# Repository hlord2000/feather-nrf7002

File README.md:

nRF7002/nRF5340 in Feather Formfactor
 * SD Card
 * Onboard flash
 * STEMMA Qt/Qwiic I2C connector
 * USB-C
 * nPM1300 regulator/battery charger

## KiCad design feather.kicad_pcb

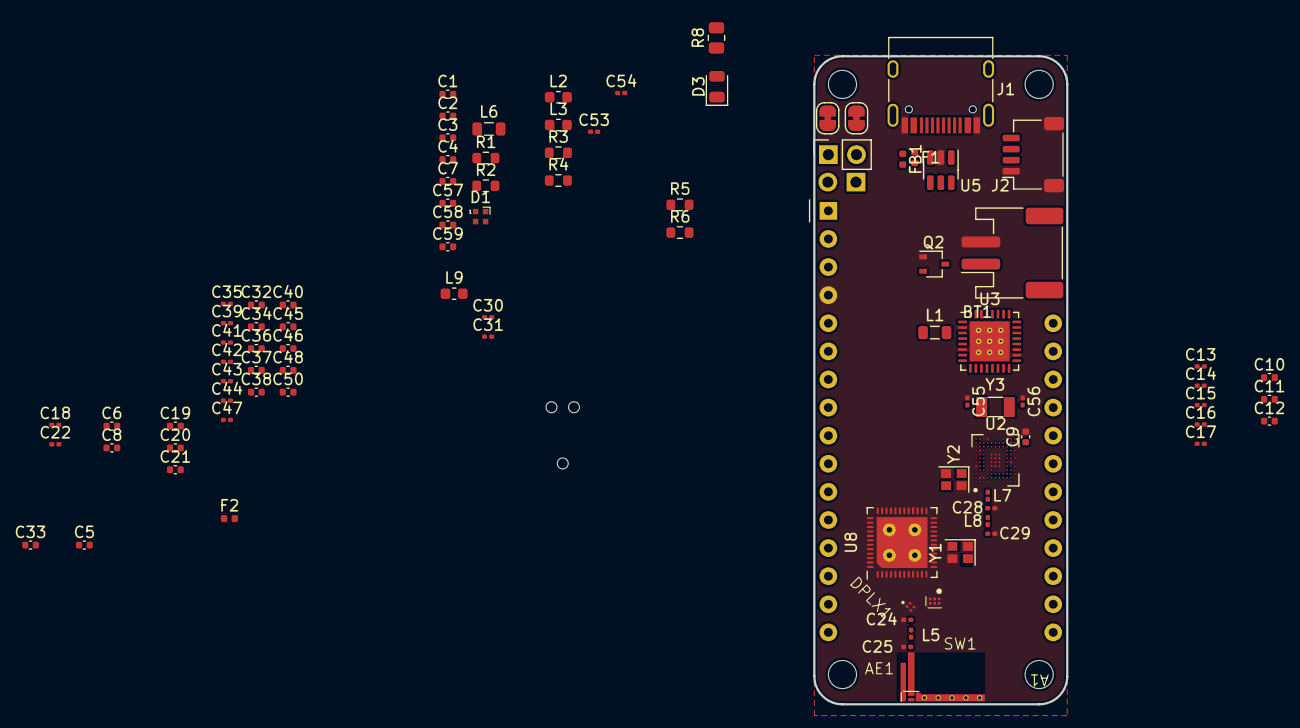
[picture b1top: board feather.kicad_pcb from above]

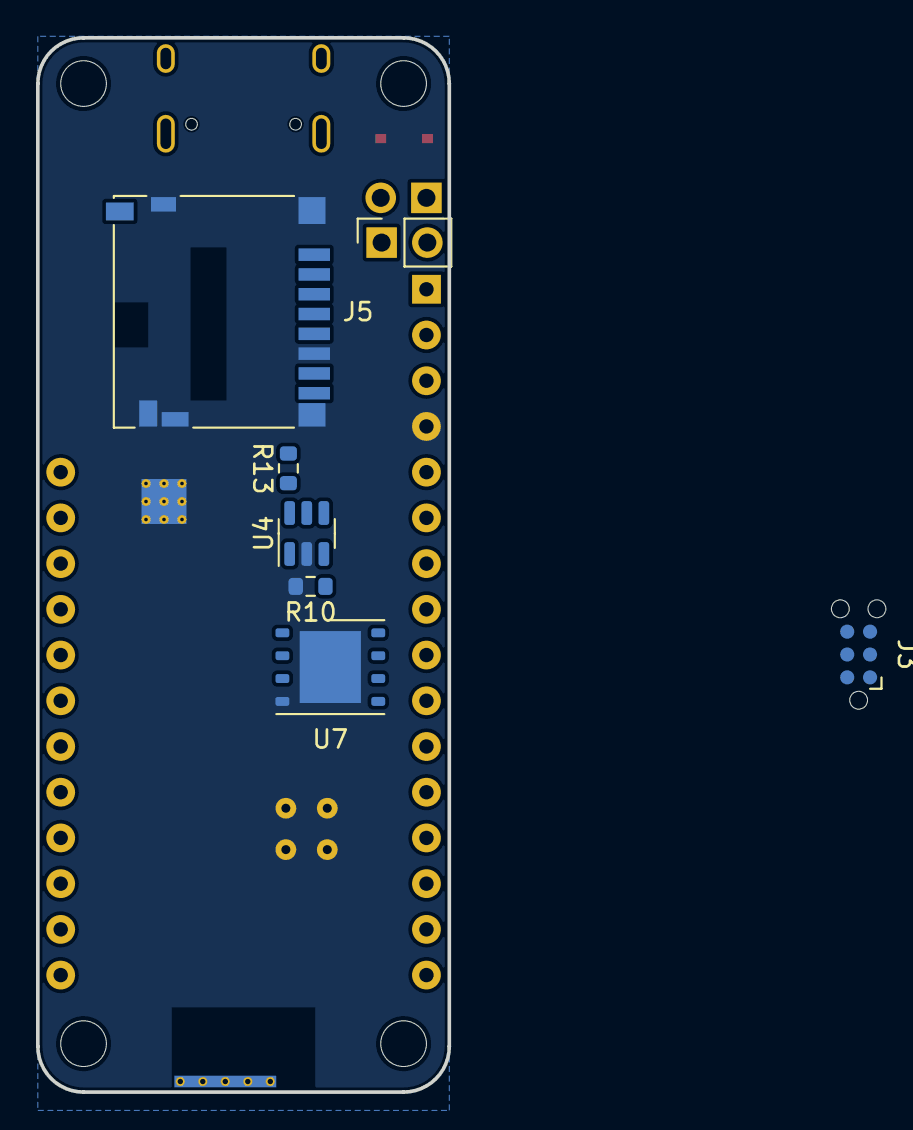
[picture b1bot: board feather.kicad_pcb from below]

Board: 4 copper layers, 22.9 x 58.6 mm, 98 parts (7 on the bottom side), 108 nets, no tracks yet.

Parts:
A1: Adafruit_Feather_Generic; Thing-Plus-Sparkfun
AE1: Capacitor_SMD:C_0402_1005Metric; 2450AD14A5500
BT1: Battery_Cell; JST_PH_S2B-PH-SM4-TB_1x02-1MP_P2.00mm_Horizontal
C1, C2, C5, C7, C57: 10u; C_0402_1005Metric
C3, C34, C40, C48: 2.2u; C_0402_1005Metric
C4, C6, C9, C10, C11, C12, C19, C21, C33, C38, C45, C46, C59: 1u; C_0402_1005Metric
C8, C20, C32, C36, C37, C50: 4.7u; C_0402_1005Metric
C13, C14, C15, C16, C17, C22, C35, C47: 100n; C_0201_0603Metric
C18: 2.2n; C_0201_0603Metric
C24, C25: C_Small; C_0201_0603Metric
C28: 0.7p; C_0201_0603Metric
C29: N.C.; C_0201_0603Metric
C30, C31: 12p; C_0201_0603Metric
C39, C42: 0.47u; C_0201_0603Metric
C41: 0.22u; C_0201_0603Metric
C43: 22n; C_0201_0603Metric
C44: 10n; C_0201_0603Metric
C53, C54, C55, C56: 8p; C_0201_0603Metric
C58: 100n; C_0402_1005Metric
D1: LED_ARGB; LED_SK6812_EC15_1.5x1.5mm
D3: LED_Small; LED_0805_2012Metric
DPLX1: DPX105950DT-6112A2
F1, F2: 1A PTC; Fuse_0402_1005Metric
FB1: FerriteBead_Small; L_0402_1005Metric
J1: USB_C_Receptacle_USB2.0; USB_C_Receptacle_HRO_TYPE-C-31-M-12
J2: Conn_01x04_MountingPin; JST_SH_SM04B-SRSS-TB_1x04-1MP_P1.00mm_Horizontal
J3: Conn_ARM_SWD_TagConnect_TC2030-NL; Tag-Connect_TC2030-IDC-NL_2x03_P1.27mm_Vertical
J4, J6: 2.54mm Header; PinSocket_1x02_P2.54mm_Vertical
J5: Micro_SD_Card_Det_Hirose_DM3AT; microSD_HC_Hirose_DM3D-SF
JP1, JP3: SolderJumper_2_Bridged; SolderJumper-2_P1.3mm_Bridged_RoundedPad1.0x1.5mm
L1, L6: 2.2u; L_0805_2012Metric
L2, L3: 10u; L_0603_1608Metric
L5: 3.3u; L_0201_0603Metric
L7, L8: 2.2n; L_0201_0603Metric
L9: 3.3u; L_0603_1608Metric
Q2: Q_PMOS_GSD; SOT-323_SC-70
R1: 47k; R_0603_1608Metric
R2: 360k; R_0603_1608Metric
R3, R4, R5, R6: 5.1k; R_0603_1608Metric
R8: 470; R_0805_2012Metric
R10: 100k; R_0603_1608Metric
R13: 33; R_0603_1608Metric
SW1: BGS12P2L6
U2: nRF5340-CLXX; BGA-132_12x11_4.39x3.994mm
U3: nPM1300-QEXX; QFN-32-1EP_5x5mm_P0.5mm_EP3.6x3.6mm_ThermalVias
U4: TPS22917DBV; SOT-23-6
U5: USBLC6-2SC6; SOT-23-6
U7: MX25R3235FZNxx1; WSON-8-1EP_6x5mm_P1.27mm_EP3.4x4mm
U8: nRF7002-QFXX; QFN-48_EP_6x6_Pitch0.4mm
Y1: 40MHz; Crystal_SMD_2016-4Pin_2.0x1.6mm
Y2: 32MHz; Crystal_SMD_2016-4Pin_2.0x1.6mm
Y3: 32.768KHz; Crystal_SMD_3215-2Pin_3.2x1.5mm

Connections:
+1V8: C1.1, L1.1, U3.1 (VOUT1)
+3V3: A1.2 (3V3), C2.1, C9.1, C10.1, C11.1, C12.1, C13.1, C14.1, C15.1, C16.1, C17.1, C34.2, C37.2, C38.2, C50.2, C58.1, J2.2, L6.1, R3.1, R4.1, R5.1, R6.1, SW1.4 (VDD), U2.A3 (VDD), U2.B7 (VDD), U2.B10 (VDD), U2.B12 (VDDH), U2.D2 (VDD), U2.E11 (VDD), U2.H11 (VDD), U2.K1 (VDD), U2.L5 (VDD), U2.L11 (VDD), U3.12 (VDDIO), U3.28 (LSIN1/VINLDO1), U3.30 (LSIN2/VINLDO2), U3.32 (VOUT2), U8.13 (VBAT), U8.20 (AFEVBAT), U8.25 (BUCKVBAT), U8.31 (BUCKVBATS)
/AIN0: A1.5 (A0), U2.G10 (P0.04/AIN0)
/AIN1: A1.6 (A1), U2.F10 (P0.05/AIN1)
/AIN2: A1.7 (A2), U2.H10 (P0.06/AIN2)
/AIN3: A1.8 (A3), U2.J10 (P0.07/AIN3)
/AIN4: A1.9 (A4), U2.L1 (P0.25/AIN4)
/AIN5: A1.10 (A5), U2.J2 (P0.26/AIN5)
/Connectivity/CC1: J1.A5 (CC1), U3.23 (CC1)
/Connectivity/CC2: J1.B5 (CC2), U3.24 (CC2)
/Connectivity/D+: J1.A6 (D+), J1.B6 (D+), U2.A12 (D+), U5.1 (I/O1), U5.6 (I/O1)
/Connectivity/D-: J1.A7 (D-), J1.B7 (D-), U2.A11 (D-), U5.3 (I/O2), U5.4 (I/O2)
/Connectivity/SOC_SWCLK: J3.4 (SWCLK), U2.F2 (SWDCLK)
/Connectivity/SOC_SWDIO: J3.2 (SWDIO), U2.F1 (SWDIO)
/FLASH_VDD: U3.29 (LSOUT1/VOUTLDO1), U7.8 (VCC)
/NRF7002_IOVDD: U3.31 (LSOUT2/VOUTLDO2), U8.48 (IOVDD)
/NonvolatileMemory/FLASH_SD_CTRL0: U2.J7 (P0.11/TRACEDATA0/~CS), U7.1 (~CS)
/NonvolatileMemory/FLASH_SD_CTRL1: J5.5 (CLK), U2.L12 (P0.08/TRACEDATA3/SCK), U7.6 (SCLK)
/NonvolatileMemory/FLASH_SD_CTRL2: J5.3 (CMD), U2.J9 (P0.09/TRACEDATA2/MOSI), U7.5 (SI/SIO0)
/NonvolatileMemory/FLASH_SD_CTRL3: J5.7 (DAT0), U2.J8 (P0.10/TRACEDATA1/MISO), U7.2 (SO/SIO1)
/NonvolatileMemory/FLASH_SD_CTRL4: J5.2 (DAT3/CD), U2.J6 (P0.12/TRACECLK/DCX)
/NonvolatileMemory/SD_CARD_EN: R10.1, U2.H1 (P0.27/AIN6), U4.3 (ON)
/NonvolatileMemory/SD_INSERTED: J5.10 (DET_A), U2.E3 (P0.28/AIN7)
/OUT0: A1.19 (D0), U2.C4 (P0.30)
/OUT1: A1.20 (D1), U2.C5 (P0.31)
/OUT2: A1.21 (D2), U2.D10 (P1.00)
/OUT3: A1.22 (D3), U2.E10 (P1.01)
/OUT4: A1.23 (D4), U2.K3 (P1.04)
/OUT5: A1.24 (D5), U2.L3 (P1.05)
/OUT6: A1.25 (D6), U2.J3 (P1.06)
/OUT7: A1.16 (SPARE), U2.G3 (P1.07)
/OUT_SPI0: A1.11 (SCK), U2.J5 (P0.19)
/OUT_SPI1: A1.12 (MOSI), U2.K5 (P0.20)
/OUT_SPI2: A1.13 (MISO), U2.J4 (P0.21)
/OUT_TWI0: A1.17 (SDA), J2.3, R5.2, U2.J11 (P1.02/TWI)
/OUT_TWI1: A1.18 (SCL), J2.4, R6.2, U2.K12 (P1.03/TWI)
/OUT_UART0: A1.14 (RX), U2.K2 (P0.24)
/OUT_UART1: A1.15 (TX), U2.E2 (P0.29)
/PowerSupply/NPM_SCL: R3.2, U2.K4 (P0.22), U3.14 (SCL)
/PowerSupply/NPM_SDA: R4.2, U2.H3 (P0.23), U3.13 (SDA)
/PowerSupply/VSYS: C5.1, C7.1, C57.1, D1.1 (A), U3.4 (PVDD), U3.20 (VSYS)
/REG_EN: A1.27 (EN), U3.7 (GPIO0)
/VBATT_: A1.28 (VBAT), C3.1, Q2.2 (S), U3.19 (VBAT)
/VBUS_: A1.26 (USB), C4.1, J6.2, JP3.2 (B), U3.21 (VBUS), U5.5 (VBUS)
/nRF5340/ANT_CTRL: SW1.6 (CTRL), U2.C10 (P1.15)
/nRF5340/NRF5340_2G4: C29.1, L8.2, SW1.1 (RF2)
/nRF5340/NRF7002_2G4: SW1.3 (RF1), U8.9 (TXRF0)
/nRF5340/NRF7002_5G: DPLX1.4 (HIGHFREQ), U8.7 (TXRF1)
/nRF5340/NRF7002_CTRL0: U2.F3 (P1.08), U8.30 (BUCKEN)
/nRF5340/NRF7002_CTRL1: U2.H2 (P1.09), U8.41 (COEX_STATUS0)
/nRF5340/NRF7002_CTRL2: U2.E4 (P1.10), U8.42 (COEX_REQ)
/nRF5340/NRF7002_CTRL3: U2.C6 (P1.11), U8.43 (COEX_GRANT)
/nRF5340/NRF7002_CTRL4: U2.C7 (P1.12), U8.46 (HOST_IRQ)
/nRF5340/NRF7002_CTRL5: U2.C8 (P1.13), U8.44 (SW_CTRL0)
/nRF5340/NRF7002_CTRL6: U2.C9 (P1.14), U8.45 (SW_CTRL1)
/nRF5340/NRF7002_QSPI0: U2.K10 (P0.13/IO0), U8.37 (QSPI_DATA0/SPI_MOSI)
/nRF5340/NRF7002_QSPI1: U2.K9 (P0.14/IO1), U8.38 (QSPI_DATA1/SPI_MISO)
/nRF5340/NRF7002_QSPI2: U2.L9 (P0.15/IO2), U8.39 (QSPI_DATA2)
/nRF5340/NRF7002_QSPI3: U2.K8 (P0.16/IO3), U8.40 (QSPI_DATA3)
/nRF5340/NRF7002_QSPI4: U2.L7 (P0.17/SCK), U8.35 (QSPI_CLK/SPI_CLK)
/nRF5340/NRF7002_QSPI5: U2.K7 (P0.18/~CS), U8.36 (QSPI_SS/SPI_SS)
/nRF7002/PWRIOVDD: C47.2, C48.2, U8.1 (OTPVDD), U8.34 (PWRIOVDD)
/nRF7002/VDD_BUCK: C32.2, C41.2, C42.2, L9.2, U8.15 (RFBUCKVDD), U8.32 (PWRBUCKVDD)
/~RESET: A1.1 (~RESET), J3.3 (~RESET), U2.G2 (~RESET)
GND: A1.4 (GND), AE1.1 (GND), BT1.2 (-), C1.2, C2.2, C3.2, C4.2, C5.2, C6.2, C7.2, C8.2, C9.2, C10.2, C11.2, C12.2, C13.2, C14.2, C15.2, C16.2, C17.2, C18.2, C19.2, C20.2, C21.2, C22.2, C24.2, C25.2, C28.2, C29.2, C30.2, C31.1, C32.1, C33.2, C34.1, C35.1, C36.1, C37.1, C38.1, C39.1, C40.1, C41.1, C42.1, C43.1, C44.1, C45.1, C46.1, C47.1, C48.1, C50.1, C53.1, C54.1, C55.1, C56.1, C57.2, C58.2, C59.2, DPLX1.1 (GND), J1.A1 (GND), J1.A12 (GND), J1.B1 (GND), J1.B12 (GND), J2.1, J2.MP (MountPin), J3.5 (GND), J5.6 (VSS), J5.9 (DET_B), J5.11 (SHIELD), Q2.1 (G), R1.2, R2.2, R8.2, R10.2, SW1.2 (GND), U2.A5 (VSS), U2.B2 (VSS), U2.B9 (VSS), U2.C2 (VSS), U2.D12 (VSS), U2.E5 (VSS), U2.E6 (VSS), U2.E7 (VSS), U2.E8 (VSS), U2.F5 (VSS), U2.F6 (VSS), U2.F7 (VSS), U2.F8 (VSS), U2.G5 (AVSS), U2.G6 (VSS), U2.G7 (VSS), U2.G8 (VSS), U2.K6 (AVSS), U2.K11 (AVSS), U3.2 (PVSS1), U3.6 (PVSS2), U3.18 (NTC), U3.33 (AVSS), U4.2 (GND), U5.2 (GND), U7.4 (GND), U7.9 (GND), U8.27 (BUCKVSS), U8.28 (BUCKVSS), U8.47 (VSS), U8.49 (EP), Y1.2, Y1.4, Y2.2, Y2.4
unnamed: AE1.2 (FEED), C25.1, L5.2
unnamed: BT1.1 (+), J4.1, JP1.1 (A)
unnamed: C28.1, L7.2, L8.1
unnamed: D1.4 (BK), U3.27 (LED2)
unnamed: D1.3 (GK), U3.26 (LED1)
unnamed: D1.2 (RK), U3.25 (LED0)
unnamed: D3.2 (A), R8.1
unnamed: D3.1 (K), F2.2, Q2.3 (D)
unnamed: C24.1, DPLX1.2 (COMMON), L5.1
unnamed: DPLX1.3 (LOWFREQ), SW1.5 (RFIN)
unnamed: F1.1, J1.A4 (VBUS), J1.A9 (VBUS), J1.B4 (VBUS), J1.B9 (VBUS)
unnamed: F1.2, FB1.1
unnamed: F2.1, J4.2, JP1.2 (B)
unnamed: C33.1, J5.4 (VDD), R13.2
unnamed: FB1.2, J6.1, JP3.1 (A)
unnamed: L7.1, U2.D1 (ANT)
unnamed: C55.2, U2.F11 (P0.00/XL1), Y3.2
unnamed: C56.2, U2.F12 (P0.01/XL2), Y3.1
unnamed: C53.2, U2.A1 (XC1), Y2.3
unnamed: C54.2, U2.A2 (XC2), Y2.1
unnamed: L2.2, U2.B6 (DCC)
unnamed: L3.2, U2.A9 (DCCD)
unnamed: C21.1, U2.B8 (DECA)
unnamed: C19.1, L3.1, U2.A7 (DECD)
unnamed: C22.1, U2.B5 (DECN)
unnamed: C6.1, C18.1, L2.1, U2.B1 (DECRF), U2.B4 (DECR)
unnamed: C20.1, U2.C11 (DECUSB)
unnamed: L1.2, U3.3 (SW1)
unnamed: L6.2, U3.5 (SW2)
unnamed: R1.1, U3.17 (VSET1)
unnamed: R2.1, U3.16 (VSET2)
unnamed: R13.1, U4.6 (VOUT)
unnamed: C46.2, U8.19 (AFELDO)
unnamed: L9.1, U8.26 (BUCKOUT)
unnamed: C44.2, U8.29 (BUCKVMID)
unnamed: C45.2, U8.33 (DIGVDD)
unnamed: C35.2, C36.2, U8.8 (PAVDD1), U8.10 (PAVDD0), U8.12 (PALDO)
unnamed: C43.2, U8.14 (RFVDD)
unnamed: C39.2, U8.11 (SXLDO)
unnamed: C40.2, U8.16 (XOLDO)
unnamed: C30.1, U8.18 (XON), Y1.1
unnamed: C31.2, U8.17 (XOP), Y1.3
VBUS: C8.1, C59.1, U2.B11 (VBUS), U3.22 (VBUSOUT)

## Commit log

2023-06-13 Initial commit.
2023-06-16 Added passvies and bus connections to nRF7002
2023-06-30 Schematic complete.
2023-06-30 removed module library.
2023-06-30 Added readme
